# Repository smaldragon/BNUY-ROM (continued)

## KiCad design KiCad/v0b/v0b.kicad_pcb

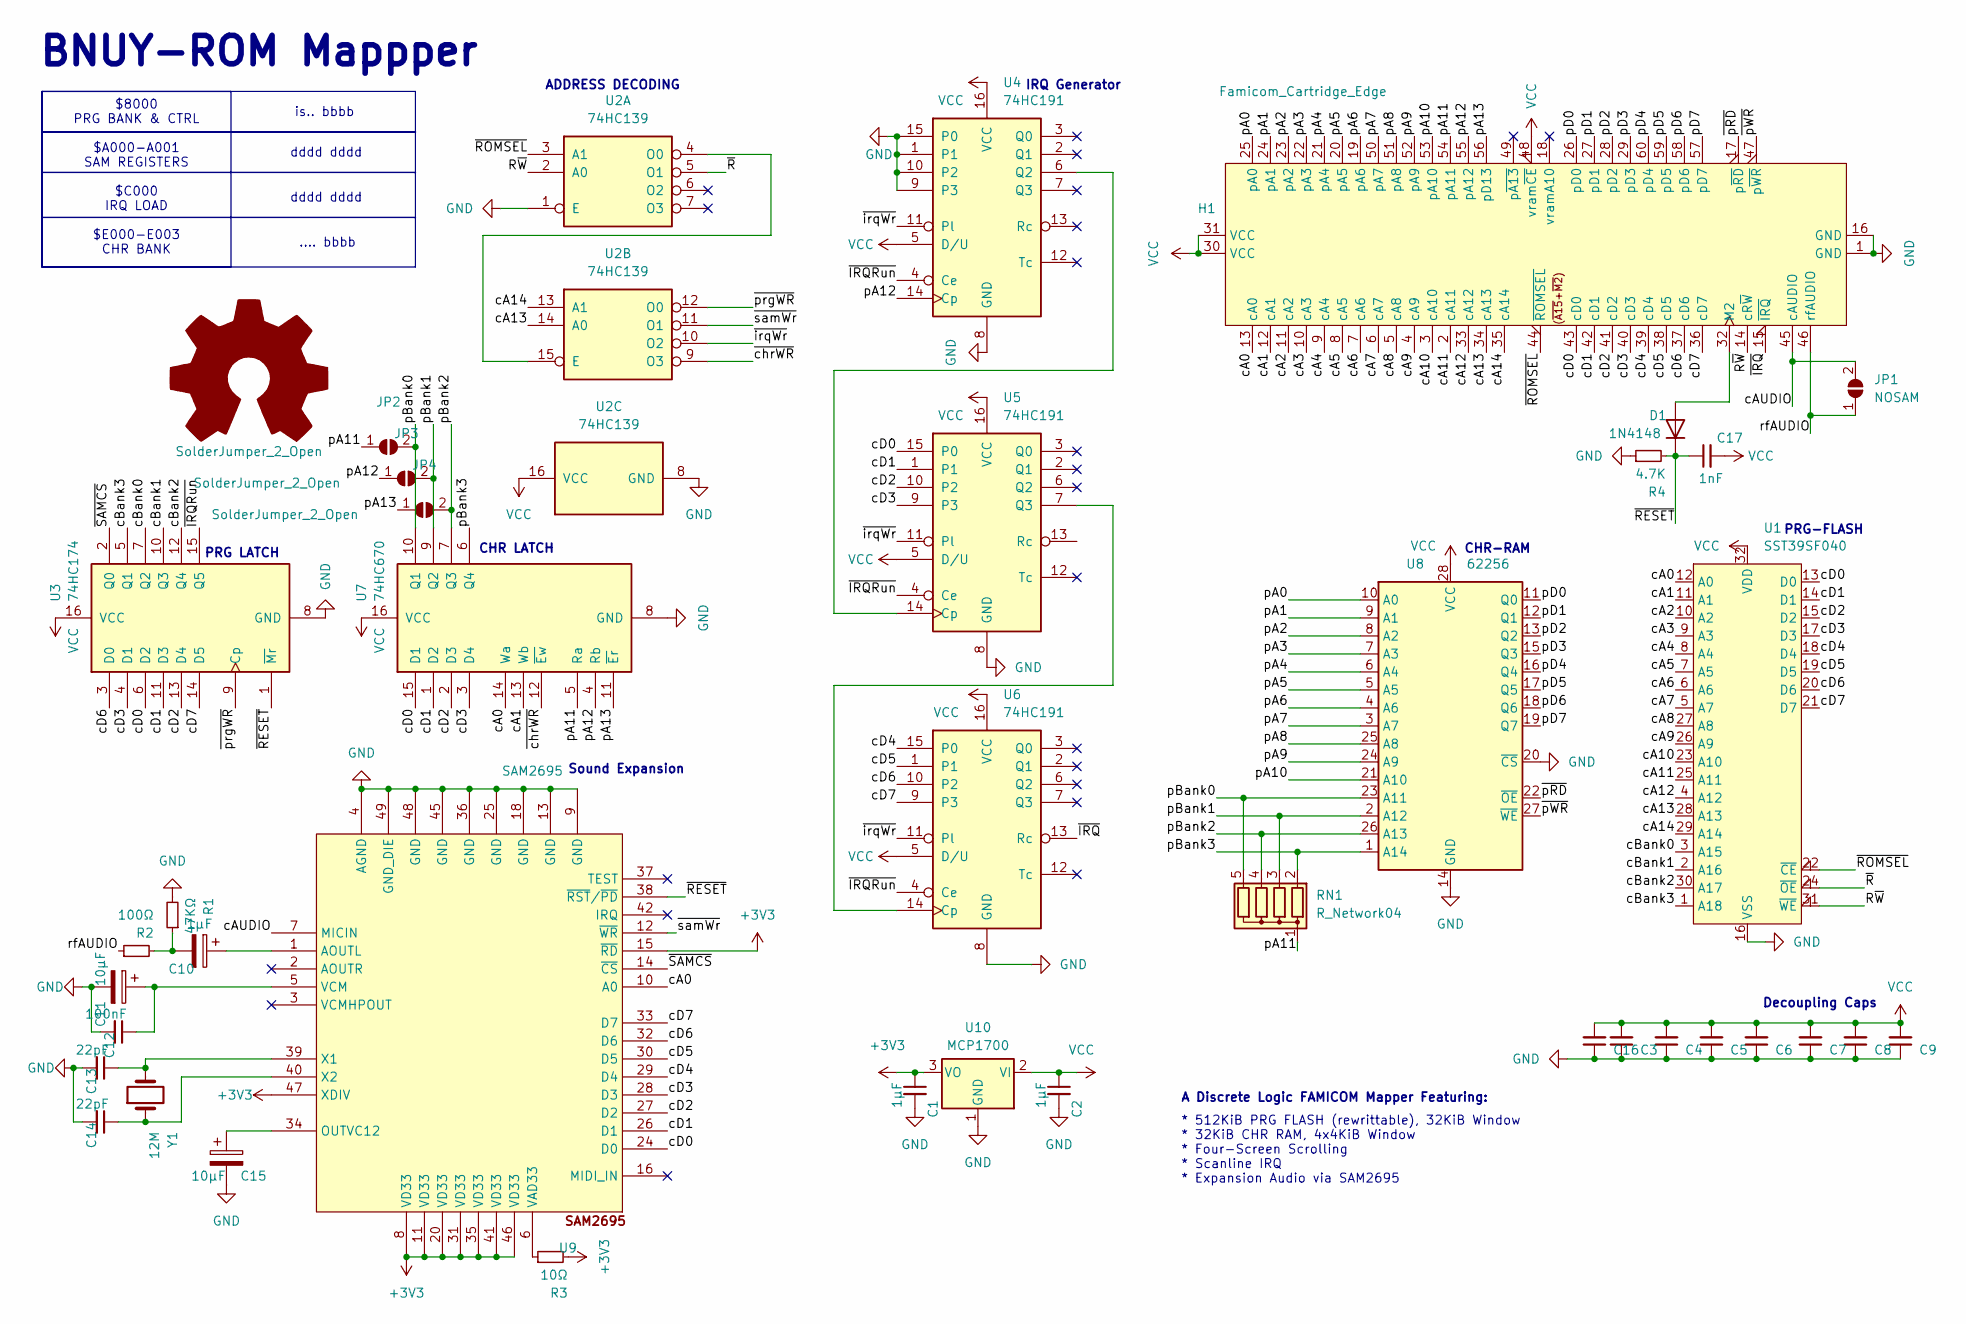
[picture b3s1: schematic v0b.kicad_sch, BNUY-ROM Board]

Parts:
C1, C2: 1µF; C_Disc_D3.0mm_W1.6mm_P2.50mm
C3, C4, C5, C6, C7, C8, C9, C16: C_Small; C_1206_3216Metric_Pad1.33x1.80mm_HandSolder
C10: 1µF; CP_Radial_D4.0mm_P1.50mm
C11, C15: 10µF; CP_Radial_D4.0mm_P1.50mm
C12: 100nF; C_Disc_D3.0mm_W1.6mm_P2.50mm
C13, C14: 22pF; C_Disc_D3.0mm_W1.6mm_P2.50mm
C17: 1nF; C_Disc_D3.0mm_W1.6mm_P2.50mm
D1: 1N4148; D_DO-34_SOD68_P2.54mm_Vertical_AnodeUp
H1: Famicom_Cartridge_Edge; Famicom Cartridge Edge Connector (long legs)
JP1: NOSAM; SolderJumper-2_P1.3mm_Open_RoundedPad1.0x1.5mm
JP2, JP3, JP4: SolderJumper_2_Open; SolderJumper-2_P1.3mm_Open_RoundedPad1.0x1.5mm
R1: 47KΩ; R_Axial_DIN0204_L3.6mm_D1.6mm_P2.54mm_Vertical
R2: 100Ω; R_Axial_DIN0204_L3.6mm_D1.6mm_P2.54mm_Vertical
R3: 10Ω; R_Axial_DIN0204_L3.6mm_D1.6mm_P2.54mm_Vertical
R4: 4.7K; R_Axial_DIN0204_L3.6mm_D1.6mm_P2.54mm_Vertical
RN1: R_Network04; R_Array_SIP5
U1: SST39SF040; DIP-32_W15.24mm_LongPads
U2: 74HC139; DIP-16_W7.62mm_LongPads
U3: 74HC174; DIP-16_W7.62mm_LongPads
U4, U5, U6: 74HC191; DIP-16_W7.62mm_LongPads
U7: 74HC670; DIP-16_W7.62mm_LongPads
U8: 62256; DIP-28_W15.24mm_LongPads
U9: SAM2695; QFN-48-1EP_6x6mm_P0.4mm_EP4.2x4.2mm_HAND
U10: MCP1700; TO-92_Inline
Y1: 12M; Crystal_HC49-4H_Vertical

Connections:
+3V3: C1.1, R3.2, U9.8 (VD33), U9.11 (VD33), U9.15 (~RD), U9.20 (VD33), U9.31 (VD33), U9.35 (VD33), U9.41 (VD33), U9.46 (VD33), U9.47 (XDIV), U10.3 (VO)
/R~W: H1.14 (cR~W), U1.31 (~WE), U2.2 (A0)
/cA0: H1.13 (cA0), U1.12 (A0), U7.14 (Wa), U9.10 (A0)
/cA1: H1.12 (cA1), U1.11 (A1), U7.13 (Wb)
/cA2: H1.11 (cA2), U1.10 (A2)
/cA3: H1.10 (cA3), U1.9 (A3)
/cA4: H1.9 (cA4), U1.8 (A4)
/cA5: H1.8 (cA5), U1.7 (A5)
/cA6: H1.7 (cA6), U1.6 (A6)
/cA7: H1.6 (cA7), U1.5 (A7)
/cA8: H1.5 (cA8), U1.27 (A8)
/cA9: H1.4 (cA9), U1.26 (A9)
/cA10: H1.3 (cA10), U1.23 (A10)
/cA11: H1.2 (cA11), U1.25 (A11)
/cA12: H1.33 (cA12), U1.4 (A12)
/cA13: H1.34 (cA13), U1.28 (A13), U2.14 (A0)
/cA14: H1.35 (cA14), U1.29 (A14), U2.13 (A1)
/cAUDIO: H1.45 (cAUDIO), JP1.2 (B), U9.7 (MICIN)
/cBank0: U1.3 (A15), U3.7 (Q2)
/cBank1: U1.2 (A16), U3.10 (Q3)
/cBank2: U1.30 (A17), U3.12 (Q4)
/cBank3: U1.1 (A18), U3.5 (Q1)
/cD0: H1.43 (cD0), U1.13 (D0), U3.6 (D2), U5.15 (P0), U7.15 (D1), U9.24 (D0)
/cD1: H1.42 (cD1), U1.14 (D1), U3.11 (D3), U5.1, U7.1 (D2), U9.26 (D1)
/cD2: H1.41 (cD2), U1.15 (D2), U3.13 (D4), U5.10 (P2), U7.2 (D3), U9.27 (D2)
/cD3: H1.40 (cD3), U1.17 (D3), U3.4 (D1), U5.9 (P3), U7.3 (D4), U9.28 (D3)
/cD4: H1.39 (cD4), U1.18 (D4), U6.15 (P0), U9.29 (D4)
/cD5: H1.38 (cD5), U1.19 (D5), U6.1, U9.30 (D5)
/cD6: H1.37 (cD6), U1.20 (D6), U3.3 (D0), U6.10 (P2), U9.32 (D6)
/cD7: H1.36 (cD7), U1.21 (D7), U3.14 (D5), U6.9 (P3), U9.33 (D7)
/pA0: H1.25 (pA0), U8.10 (A0)
/pA1: H1.24 (pA1), U8.9 (A1)
/pA2: H1.23 (pA2), U8.8 (A2)
/pA3: H1.22 (pA3), U8.7 (A3)
/pA4: H1.21 (pA4), U8.6 (A4)
/pA5: H1.20 (pA5), U8.5 (A5)
/pA6: H1.19 (pA6), U8.4 (A6)
/pA7: H1.50 (pA7), U8.3 (A7)
/pA8: H1.51 (pA8), U8.25 (A8)
/pA9: H1.52 (pA9), U8.24 (A9)
/pA10: H1.53 (pA10), U8.21 (A10)
/pA11: H1.54 (pA11), JP2.1 (A), RN1.1 (common), U7.5 (Ra)
/pA12: H1.55 (pA12), JP3.1 (A), U4.14 (Cp), U7.4 (Rb)
/pA13: H1.56 (pD13), JP4.1 (A), U7.11 (~Er)
/pBank0: JP2.2 (B), RN1.5 (R4), U7.10 (Q1), U8.23 (A11)
/pBank1: JP3.2 (B), RN1.3 (R2), U7.9 (Q2), U8.2 (A12)
/pBank2: JP4.2 (B), RN1.4 (R3), U7.7 (Q3), U8.26 (A13)
/pBank3: RN1.2 (R1), U7.6 (Q4), U8.1 (A14)
/pD0: H1.26 (pD0), U8.11 (Q0)
/pD1: H1.27 (pD1), U8.12 (Q1)
/pD2: H1.28 (pD2), U8.13 (Q2)
/pD3: H1.29 (pD3), U8.15 (Q3)
/pD4: H1.60 (pD4), U8.16 (Q4)
/pD5: H1.59 (pD5), U8.17 (Q5)
/pD6: H1.58 (pD6), U8.18 (Q6)
/pD7: H1.57 (pD7), U8.19 (Q7)
/rfAUDIO: H1.46 (rfAUDIO), JP1.1 (A), R2.1
/~IRQRun: U3.15 (Q5), U4.4 (Ce), U5.4 (Ce), U6.4 (Ce)
/~IRQ: H1.15 (~IRQ), U6.13 (Rc)
/~RESET: C17.1, D1.1 (K), R4.2, U3.1 (~Mr), U9.38 (~RST/~PD)
/~ROMSEL: H1.44 (~ROMSEL), U1.22 (~CE), U2.3 (A1)
/~R: U1.24 (~OE), U2.5 (O1)
/~SAMCS: U3.2 (Q0), U9.14 (~CS)
/~chrWR: U2.9 (O3), U7.12 (~Ew)
/~irqWr: U2.10 (O2), U4.11 (Pl), U5.11 (Pl), U6.11 (Pl)
/~pRD: H1.17 (p~RD), U8.22 (~OE)
/~pWR: H1.47 (p~WR), U8.27 (~WE)
/~prgWR: U2.12 (O0), U3.9 (Cp)
/~samWr: U2.11 (O1), U9.12 (~WR)
GND: C1.2, C2.2, C3.1, C4.1, C5.1, C6.1, C7.1, C8.1, C9.1, C11.2, C12.2, C13.2, C14.2, C15.2, C16.1, H1.1 (GND), H1.16 (GND), R1.2, R4.1, U1.16 (VSS), U2.1 (E), U2.8 (GND), U3.8 (GND), U4.1, U4.8 (GND), U4.9 (P3), U4.10 (P2), U4.15 (P0), U5.8 (GND), U6.8 (GND), U7.8 (GND), U8.14 (GND), U8.20 (~CS), U9.4 (AGND), U9.9 (GND), U9.13 (GND), U9.18 (GND), U9.25 (GND), U9.36 (GND), U9.45 (GND), U9.48 (GND), U9.49 (GND_DIE), U10.1 (GND)
unnamed: C10.2, R1.1, R2.2
unnamed: D1.2 (A), H1.32 (M2)
unnamed: U2.4 (O0), U2.15 (E)
unnamed: U4.6 (Q2), U5.14 (Cp)
unnamed: U5.7 (Q3), U6.14 (Cp)
unnamed: C10.1, U9.1 (AOUTL)
unnamed: C15.1, U9.34 (OUTVC12)
unnamed: R3.1, U9.6 (VAD33)
unnamed: C11.1, C12.1, U9.5 (VCM)
unnamed: C13.1, U9.39 (X1), Y1.2
unnamed: C14.1, U9.40 (X2), Y1.1
VCC: C2.1, C3.2, C4.2, C5.2, C6.2, C7.2, C8.2, C9.2, C16.2, C17.2, H1.30 (VCC), H1.31 (VCC), H1.48 (vram~CE), U1.32 (VDD), U2.16 (VCC), U3.16 (VCC), U4.5 (D/U), U4.16 (VCC), U5.5 (D/U), U5.16 (VCC), U6.5 (D/U), U6.16 (VCC), U7.16 (VCC), U8.28 (VCC), U10.2 (VI)

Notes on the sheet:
$8000 PRG BANK & CTRL $A000-A001 SAM REGISTERS $C000 IRQ LOAD $E000-E003 CHR BANK
BNUY-ROM Mappper
is.. bbbb
* 512KiB PRG FLASH (rewrittable), 32KiB Window * 32KiB CHR RAM, 4x4KiB Window * Four-Screen Scrolling * Scanline IRQ * Expansion Audio via SAM2695
ADDRESS DECODING
CHR-RAM
dddd dddd
.... bbbb
CHR LATCH
A Discrete Logic FAMICOM Mapper Featuring:
Decoupling Caps
PRG-FLASH
PRG LATCH
Sound Expansion
IRQ Generator

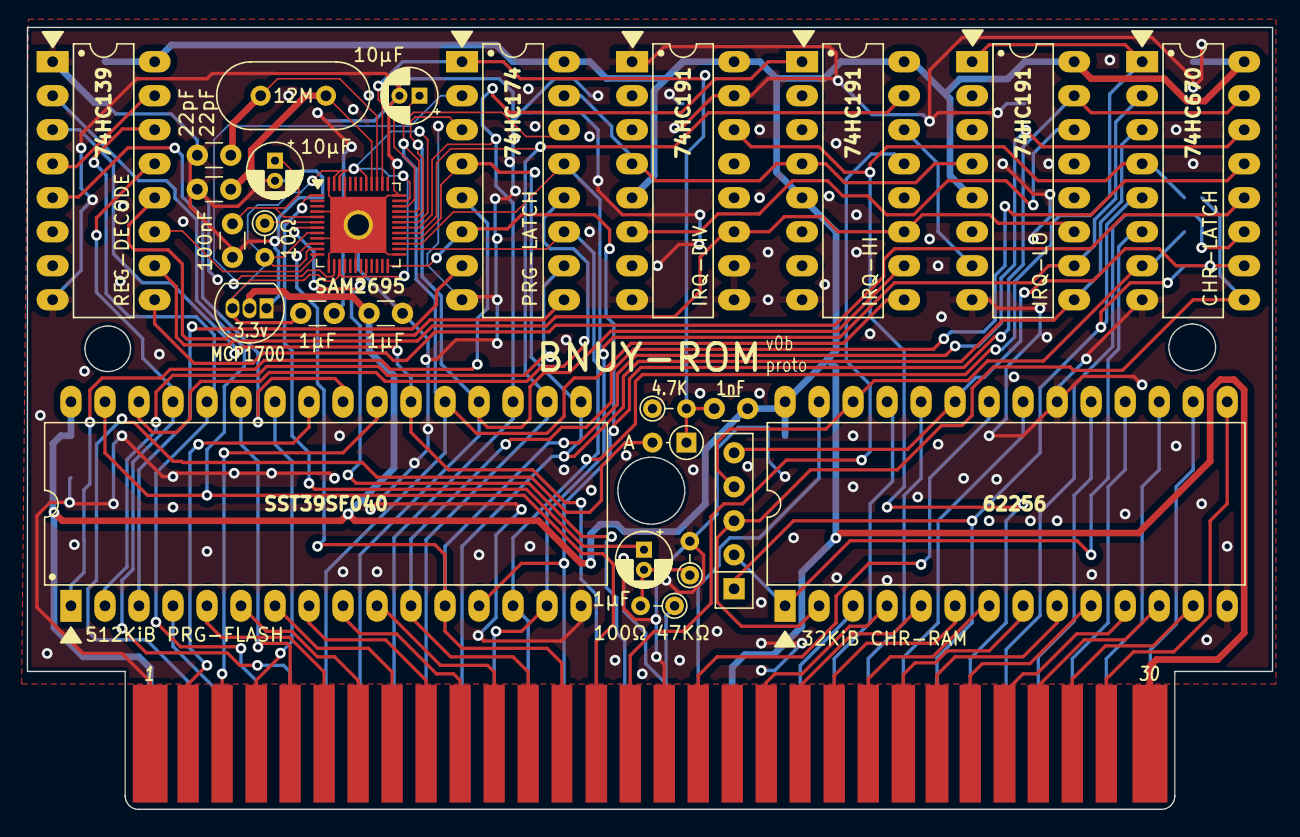
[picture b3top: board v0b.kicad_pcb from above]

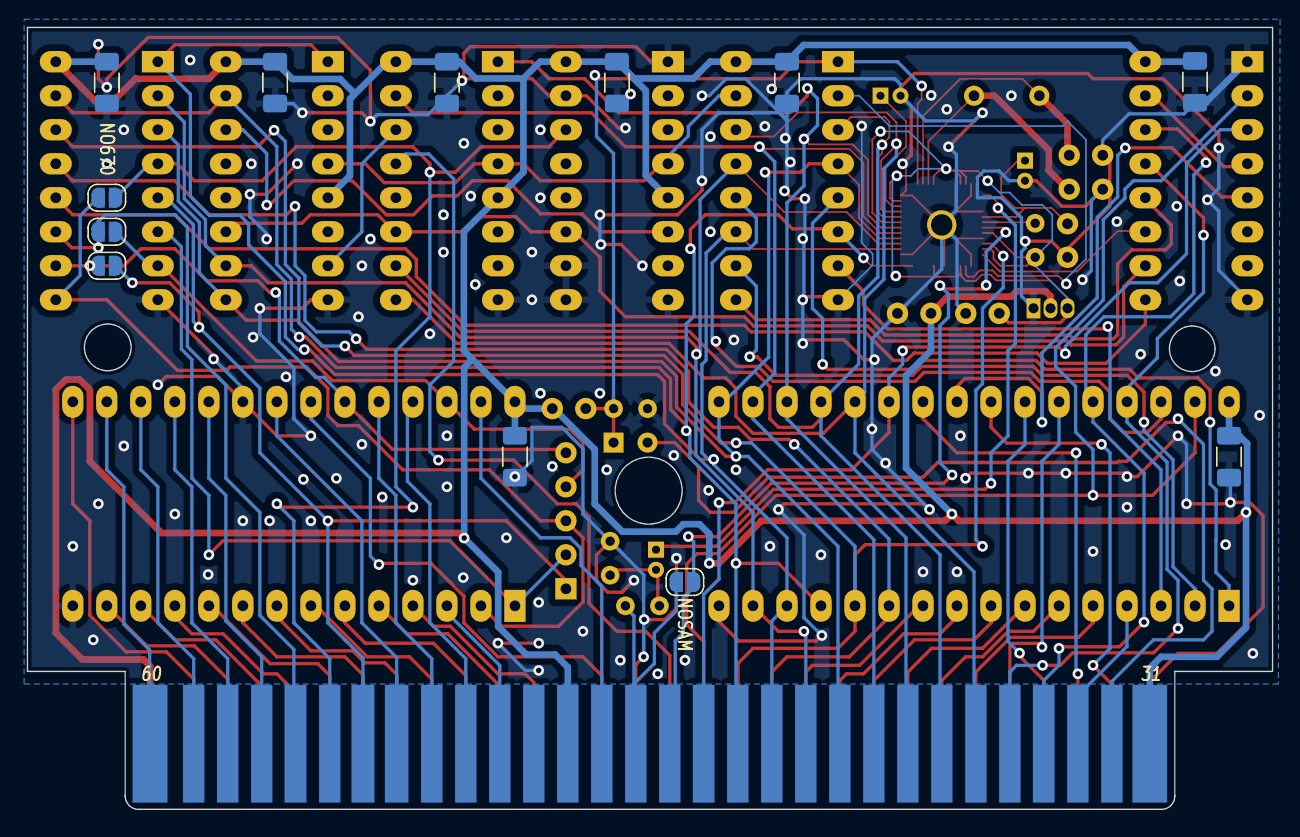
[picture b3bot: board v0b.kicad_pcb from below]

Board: 2 copper layers, 93.0 x 58.4 mm, 39 parts (12 on the bottom side), 82 nets.

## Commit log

2024-03-09 Add pcb files
2024-03-09 add render image
2024-03-31 v0b update
2024-04-01 update v0b and README documentation
2024-04-03 update v0b
2025-04-03 Update README, v0b schematic
2025-06-04 initial v0c update
2025-06-06 sam2695 on board
2025-06-06 Silkscreen and schematic tweaks
2025-06-30 Change Scanline Circuit
2025-07-08 Update with new irq and chr128 behaviour
2025-07-10 Update pcbs and readme
2025-07-23 Update README.md (oh god)
2025-07-26 Update README.md
    More alternatives
2025-07-29 Fix broken commit
2025-07-29 minor typo
2025-07-29 timing clarification
2025-07-30 fix issues
2025-07-31 Update README.md
    some more clarifications
2025-08-05 v0d smd board
2025-08-05 schematic tweak
2025-09-10 Add a tentative description for a NES 2.0 header
2026-01-14 Update to latest pcb version, README tweaks
2026-01-15 Add FLASH programming details to README.md
2026-01-17 add battery bit flag to README
